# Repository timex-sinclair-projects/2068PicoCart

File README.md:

# 2068 PicoCart

A dock cartridge for the Timex Sinclair 2068, built around a Raspberry Pi RP2354B (RP2350 with 2 MB of flash in the package). It emulates the cartridge ROM and RAM in the dock bank. To load a cart, plug the cart into your computer with USB-C and copy a `.dck` or `.bin` file onto it as if it were a thumb drive.

| Top | Bottom |
|:---:|:---:|
|  |  |

## Features

- **Thumb-drive loading.** Over USB the cart appears as a 1.4 MB drive called `PICOCART`. Copy a cart onto it, then switch the 2068 off and on. The cart serves the file you copied most recently and remembers it across power cycles.
- **A cartridge icon on the Mac.** In the Finder the `PICOCART` drive shows a cartridge icon ([`firmware/romemu/icon`](firmware/romemu/icon)). The firmware adds the two hidden files that make it, `.VolumeIcon.icns` and `._.`, whenever they're missing.
- **AROS and LROS images.** Supports `.dck` files (the EightyOne/Warajevo dock format, including RAM chunks) and raw `.bin`/`.rom` images. A raw image loads at $8000 unless its name gives an address, for example `GAME@0000.BIN`.
- **Full-speed bus emulation.** One RP2350 core does nothing but serve the bus. It runs from SRAM with interrupts off and handles about 650,000 dock reads per second in the 2068.
- **On-screen cart menu.** Hold **MENU** while switching the 2068 on, and it shows a list of the carts on the drive. Pick one with the cursor keys (or Q/A) and ENTER, and the 2068 restarts into that cart, with no power cycle. Pressing MENU while the 2068 runs brings the menu up at the next power-up instead, even with no USB power in between. The first entry starts the 2068 in BASIC with the cart off the bus.
- **No USB needed in the 2068.** The cart runs on the 2068's own +5 V. USB is only for copying carts onto it, and the cart can be powered by USB alone for that.
- **Safe on the bus.** The 74LVC245 data buffer stays off until the cart sees the 2068's +5 V hold steady.
- **USB serial.** Status and debug output come over the same USB-C cable. `picotool load -f` can reflash the cart without pressing BOOTSEL.

## Hardware

- 4-layer board: signal, GND, +3V3, signal. KiCad 10 project in [`hardware/`](hardware).
- RP2354B, 74LVC245 buffer on the data bus, a 74LVC1G332 for buffer enable, a 3.3 V LDO, USB-C, and two buttons: MENU and BOOTSEL.
- Red LED = cart on the bus. White LED = dock activity. R15, the white LED's resistor, is 3.3 kΩ; rev 0.1 boards have 100 Ω.
- The board and the routing are generated by scripts in [`hardware/scripts`](hardware/scripts). The pinout and BOM are in [SCHEMATIC.md](SCHEMATIC.md); the design notes are in [PLAN.md](PLAN.md).
- JLCPCB Gerbers, BOM and placement file for **rev 0.2** are in [`hardware/fab/jlcpcb`](hardware/fab/jlcpcb). Rev 0.2 differs from rev 0.1 in the MENU/BOOT labels, R15 = 3.3 kΩ, no OLED header, and "rev 0.2" on the underside. Read [hardware/fab/NOTES.md](hardware/fab/NOTES.md) before ordering. It covers the finger bevel, the parts that aren't assembled, and the L1 orientation.

### GPIO map

| GPIO | Signal |
|---|---|
| 0–15 | A0–A15 |
| 16–23 | MD0–MD7 (MCU side of the 74LVC245) |
| 24–31 | ROSCS, MREQ, RD, WR, IORQ, M1, RFSH, EXROM |
| 32 | BUS_OFF (high = buffer off) |
| 33 | BE (via the R10 link, not fitted) |
| 37 | A7R |
| 40 / 41 | DOCK +5 V and VBUS sense (ADC, 10k/15k dividers) |
| 43 / 44 | White / red LED |
| 45 | MENU button |
| 46 / 47 | UART TX / RX (test pads) |

## Firmware

Two programs are in [`firmware/`](firmware). Both use the board header in [`firmware/boards`](firmware/boards):

- [`bringup`](firmware/bringup) checks a new board. It holds the bus buffer off, then reports the +5 V rails, activity on the bus lines, and the MD float test over USB serial.
- [`romemu`](firmware/romemu) is the cartridge firmware. The cart menu is Z80 code in [`romemu/menu`](firmware/romemu/menu). The build reassembles it with [sjasmplus](https://github.com/z00m128/sjasmplus) when that's installed, and otherwise uses the committed `menu.bin`.

### Bus behaviour

[BUS.md](BUS.md) sets out exactly when the cart drives the 2068's buses, with references to the schematic and firmware. Read it if you're combining the cart with other hardware on the bus, such as a TS-Pico on the rear expansion port.

### How the menu works

The menu is a machine-code AROS cart that the firmware serves at $8000, with a directory table at $9000 that lists the carts on the drive. When you choose one, the menu copies a short routine into HOME RAM and runs it from there. The routine writes the entry number to $BFFF in the dock, the cart's mailbox. It then waits about a second while the firmware swaps in the chosen cart, pages HOME back in and jumps to $0000. The 2068 starts up again and reads the new cart's header. [`firmware/tests/menu_dck.py`](firmware/tests/menu_dck.py) builds the menu with a test directory as a `.dck`, for trying it in an emulator such as ZEsarUX.

### Build

You need the Pico SDK 2.2.0 or later, the Arm GNU toolchain, CMake, Ninja and picotool.

```bash
export PICO_SDK_PATH=~/pico-sdk PICO_TOOLCHAIN_PATH=~/arm-gnu-toolchain
cmake -S firmware/romemu -B firmware/romemu/build -G Ninja
ninja -C firmware/romemu/build
picotool load -f -x firmware/romemu/build/romemu.uf2
```

The first time, hold BOOTSEL while plugging in USB; after that, `picotool load -f` reboots the cart itself.

The white LED (D4) runs at 3% brightness by default, to suit rev 0.1 boards, where R15 is 100 Ω. On boards built from the current design (R15 = 3.3 kΩ), build with `-DLED2_PERCENT=100`:

```bash
cmake -S firmware/romemu -B firmware/romemu/build -DLED2_PERCENT=100
```

Optionally, you can compile a fallback image into the firmware. The cart serves it when the drive has no cart on it:

```bash
cmake -S firmware/romemu -B firmware/romemu/build -DROM_IMAGE="path/to/cart.dck"
```

### Flash layout

| Offset | Use |
|---|---|
| 0x000000 | Firmware (up to 512 KB) |
| 0x080000 | `PICOCART` drive: FAT12, 1.4 MB |
| 0x1FE000 | Settings log, two 4 KB sectors: the current cart, and whether the menu comes up at the next power-up |

On first boot the firmware formats the drive and puts a `README.TXT` on it. If the drive gets corrupted, reformat it from your computer as FAT.

## Using it

The full user's manual is in [`docs/manual`](docs/manual): [read it on screen](docs/manual/2068%20PicoCart%20Manual.html), or print the [half-letter PDF](docs/manual/2068%20PicoCart%20Manual%20(half-letter).pdf) or the [duplex booklet](docs/manual/2068%20PicoCart%20Manual%20(booklet,%20print%20duplex).pdf). For a booklet with a card cover, print the [card-cover booklet](docs/manual/2068%20PicoCart%20Manual%20(booklet%20with%20card%20cover,%20print%20duplex).pdf): its first sheet is the cover, with blank inside covers, so you can print that sheet on card.

1. Plug the cart into your computer. The `PICOCART` drive appears.
2. Copy a `.dck`, `.bin` or `.rom` file onto it, then eject the drive.
3. Switch the 2068 off and on. The 2068 reads the dock only at power-up.

If the 2068 is running when you copy, the cart keeps serving the old cart until the 2068 is switched off. Both LEDs blink together while a new cart is waiting.

To switch between carts already on the drive, hold MENU while switching the 2068 on and pick one from the list. The cart you pick stays the current cart until you pick or copy another.

### Without USB

The cart doesn't need USB in the 2068. It runs on the 2068's +5 V and remembers everything in flash: the carts on the drive, the current cart, and a MENU press made while the 2068 was on. So you can fill the drive once and leave the cable at your computer:

1. Plug the cart into your computer on its own, with no 2068. USB powers it, and the `PICOCART` drive appears.
2. Copy carts onto it, eject the drive and unplug the cable.
3. Put the cart in the 2068 and switch it on. Choose carts with the menu.

From the 2068's power alone, the cart's firmware is running 0.1 ms after power reaches it, and the cart serves the bus about 1.8 s before the 2068 first reads the dock. You can plug USB in while the 2068 is on, for example to watch the serial status; the cart keeps running.

## Status

Rev 0.1 boards have been built and brought up. These carts run from the cart's ROM: AROS BASIC carts (Hello world, and Profile 2068's 16K at $8000–$BFFF), 32K machine-code carts (73000 Flight Simulator), and LROS carts that replace the HOME ROM (Space Raiders, 16K at $0000–$3FFF). RAM in the dock bank works: [`firmware/tests/ramtest.py`](firmware/tests/ramtest.py) builds a test cart that writes and checks two patterns across 8 KB of cart RAM at $C000. It passes, and the cart counted exactly 16,384 dock writes. Loading from the USB drive works. The cart runs on the 2068's power alone, with no USB. The on-screen cart menu works on the 2068: choosing a cart restarts the 2068 into it, and the "no cartridge" entry starts BASIC with the cart off the bus. Pressing MENU while a cart runs brings up the menu at the next power-up, with or without USB power in between, and a second press cancels it. Every feature has now been tested on hardware.

Rev 0.2 is designed but not yet built. Its fab files are in [`hardware/fab/jlcpcb`](hardware/fab/jlcpcb). The changes are small and come from using rev 0.1:
- MENU and BOOT labels on the silkscreen by the buttons.
- R15, the white LED's resistor, is 3.3 kΩ instead of 100 Ω. At 100 Ω the white LED was far brighter than the red one; rev 0.1 firmware dims it to 3% with PWM instead. Build the firmware for rev 0.2 with `-DLED2_PERCENT=100`.
- No OLED header. The dock covers that part of the board, so a display there could not be seen. GPIO34 and GPIO35 are now spare.
- "2068 PicoCart rev 0.2" on the underside, so the two revisions can be told apart.

The circuit and routing are otherwise the same as rev 0.1, so rev 0.2 should behave the same. Still to check when the boards arrive: the white LED's brightness at 3.3 kΩ.

## License

The hardware is licensed under [CERN-OHL-P-2.0](hardware/LICENSE) and the firmware under [MIT](firmware/LICENSE). See [LICENSE.md](LICENSE.md) for details.

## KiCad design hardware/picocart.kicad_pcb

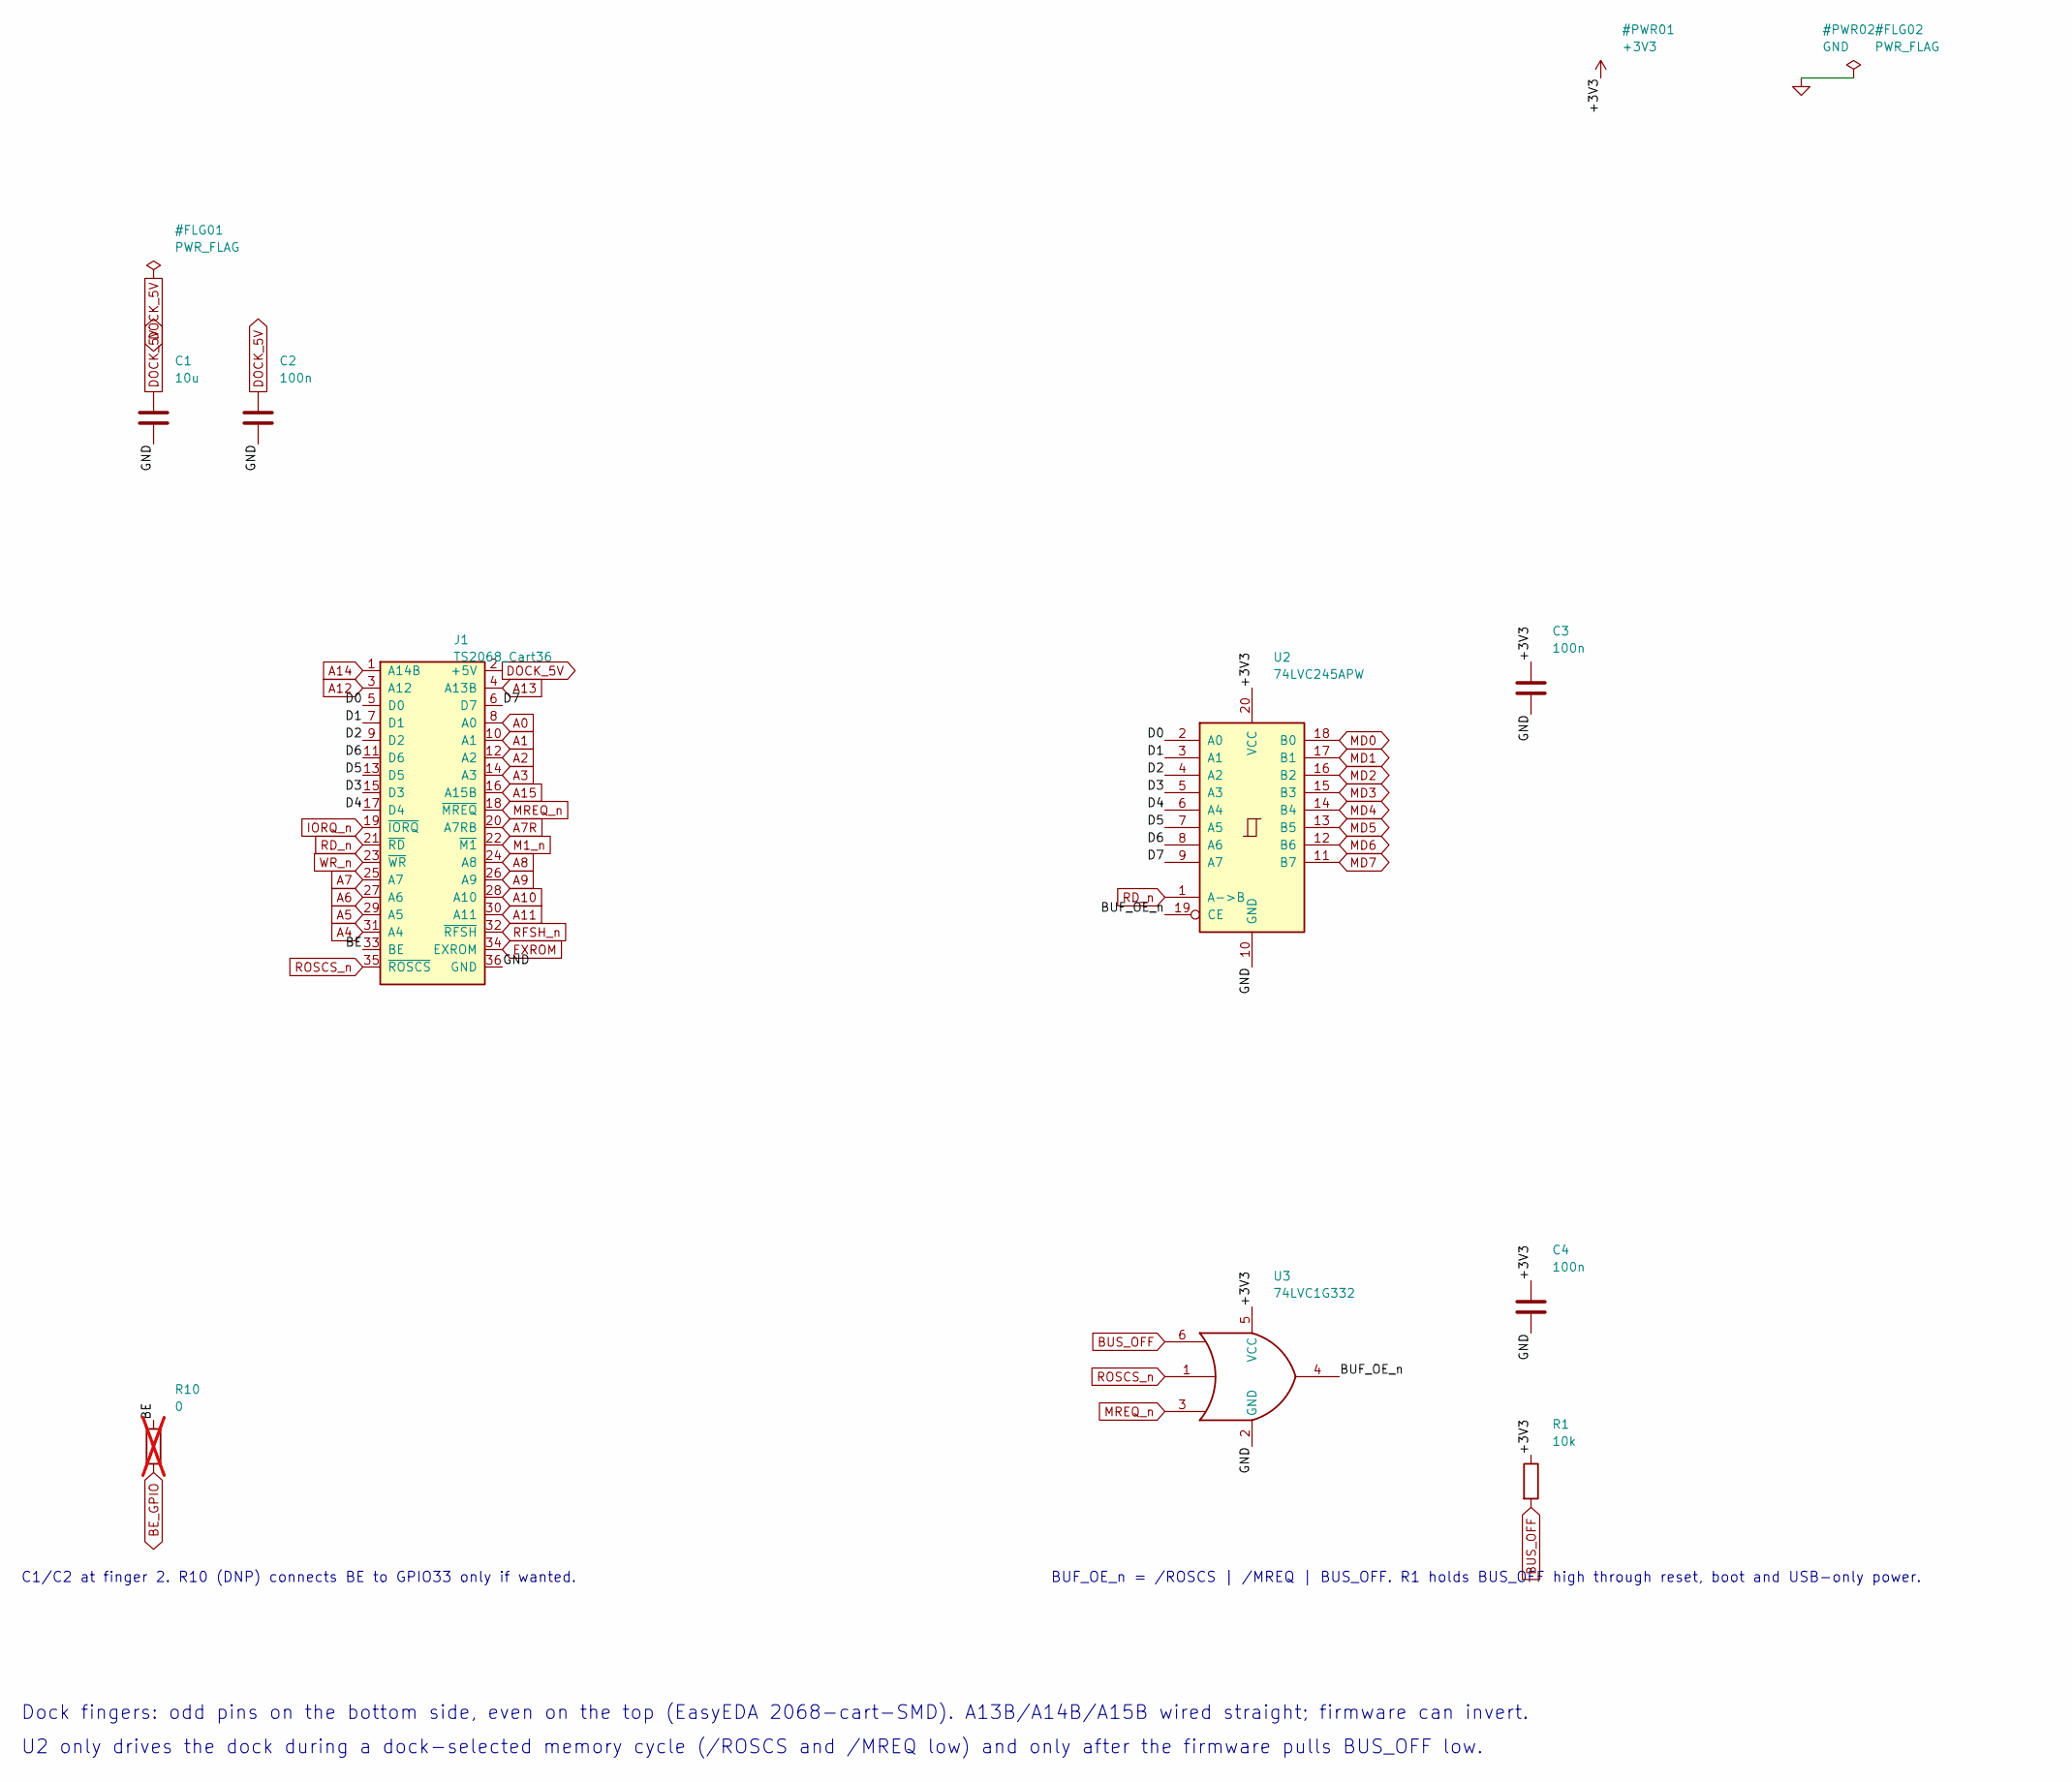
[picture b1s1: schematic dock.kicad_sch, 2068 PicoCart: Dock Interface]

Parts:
C1: 10u; C_0805_2012Metric; MPN CL21A106KAYNNNE; LCSC C15850
C2, C3, C4: 100n; C_0603_1608Metric; MPN CC0603KRX7R9BB104; LCSC C14663
J1: TS2068_Cart36
R1: 10k; R_0603_1608Metric; MPN 0603WAF1002T5E; LCSC C25804
R10: 0; R_0603_1608Metric; MPN 0603WAF0000T5E; LCSC C21189; not fitted
U2: 74LVC245APW; TSSOP-20_4.4x6.5mm_P0.65mm; MPN 74LVC245APW,118; LCSC C6082
U3: 74LVC1G332; SOT-363_SC-70-6; MPN 74LVC1G332GW,125; LCSC C548342

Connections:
+3V3: C3.1, C4.1, R1.1, U2.20 (VCC), U3.5 (VCC); also elsewhere on the board
/Dock Interface/BE: J1.33 (BE), R10.1
/Dock Interface/BUF_OE_n: U2.19 (CE), U3.4
/Dock Interface/D0: J1.5 (D0), U2.2 (A0)
/Dock Interface/D1: J1.7 (D1), U2.3 (A1)
/Dock Interface/D2: J1.9 (D2), U2.4 (A2)
/Dock Interface/D3: J1.15 (D3), U2.5 (A3)
/Dock Interface/D4: J1.17 (D4), U2.6 (A4)
/Dock Interface/D5: J1.13 (D5), U2.7 (A5)
/Dock Interface/D6: J1.11 (D6), U2.8 (A6)
/Dock Interface/D7: J1.6 (D7), U2.9 (A7)
A0: J1.8 (A0); also elsewhere on the board
A1: J1.10 (A1); also elsewhere on the board
A2: J1.12 (A2); also elsewhere on the board
A3: J1.14 (A3); also elsewhere on the board
A4: J1.31 (A4); also elsewhere on the board
A5: J1.29 (A5); also elsewhere on the board
A6: J1.27 (A6); also elsewhere on the board
A7: J1.25 (A7); also elsewhere on the board
A7R: J1.20 (A7RB); also elsewhere on the board
A8: J1.24 (A8); also elsewhere on the board
A9: J1.26 (A9); also elsewhere on the board
A10: J1.28 (A10); also elsewhere on the board
A11: J1.30 (A11); also elsewhere on the board
A12: J1.3 (A12); also elsewhere on the board
A13: J1.4 (A13B); also elsewhere on the board
A14: J1.1 (A14B); also elsewhere on the board
A15: J1.16 (A15B); also elsewhere on the board
BE_GPIO: R10.2; also elsewhere on the board
BUS_OFF: R1.2, U3.6; also elsewhere on the board
DOCK_5V: C1.1, C2.1, J1.2 (+5V); also elsewhere on the board
EXROM: J1.34 (EXROM); also elsewhere on the board
GND: C1.2, C2.2, C3.2, C4.2, J1.36 (GND), U2.10 (GND), U3.2 (GND); also elsewhere on the board
IORQ_n: J1.19 (~IORQ); also elsewhere on the board
M1_n: J1.22 (~M1); also elsewhere on the board
MD0: U2.18 (B0); also elsewhere on the board
MD1: U2.17 (B1); also elsewhere on the board
MD2: U2.16 (B2); also elsewhere on the board
MD3: U2.15 (B3); also elsewhere on the board
MD4: U2.14 (B4); also elsewhere on the board
MD5: U2.13 (B5); also elsewhere on the board
MD6: U2.12 (B6); also elsewhere on the board
MD7: U2.11 (B7); also elsewhere on the board
MREQ_n: J1.18 (~MREQ), U3.3; also elsewhere on the board
RD_n: J1.21 (~RD), U2.1 (A->B); also elsewhere on the board
RFSH_n: J1.32 (~RFSH); also elsewhere on the board
ROSCS_n: J1.35 (~ROSCS), U3.1; also elsewhere on the board
WR_n: J1.23 (~WR); also elsewhere on the board

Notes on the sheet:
Dock fingers: odd pins on the bottom side, even on the top (EasyEDA 2068-cart-SMD). A13B/A14B/A15B wired straight; firmware can invert.
U2 only drives the dock during a dock-selected memory cycle (/ROSCS and /MREQ low) and only after the firmware pulls BUS_OFF low.
C1/C2 at finger 2. R10 (DNP) connects BE to GPIO33 only if wanted.
BUF_OE_n = /ROSCS | /MREQ | BUS_OFF. R1 holds BUS_OFF high through reset, boot and USB-only power.

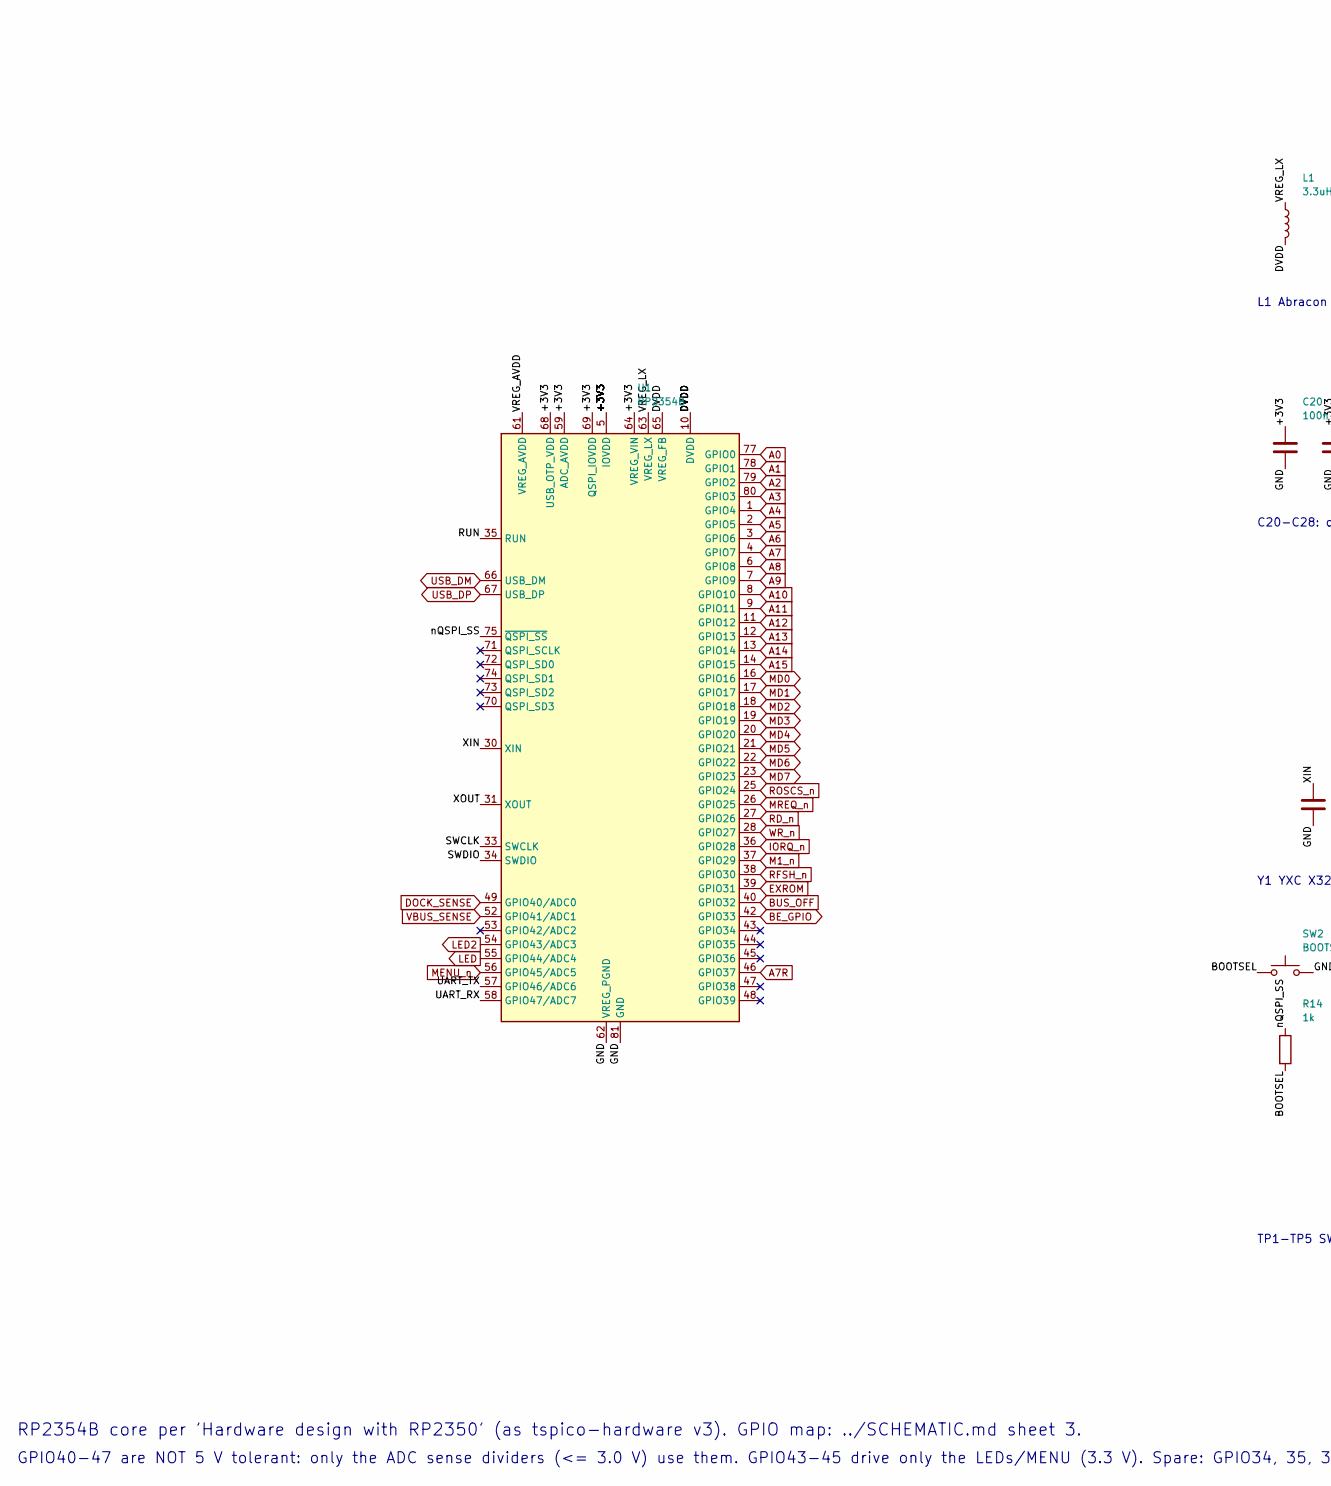
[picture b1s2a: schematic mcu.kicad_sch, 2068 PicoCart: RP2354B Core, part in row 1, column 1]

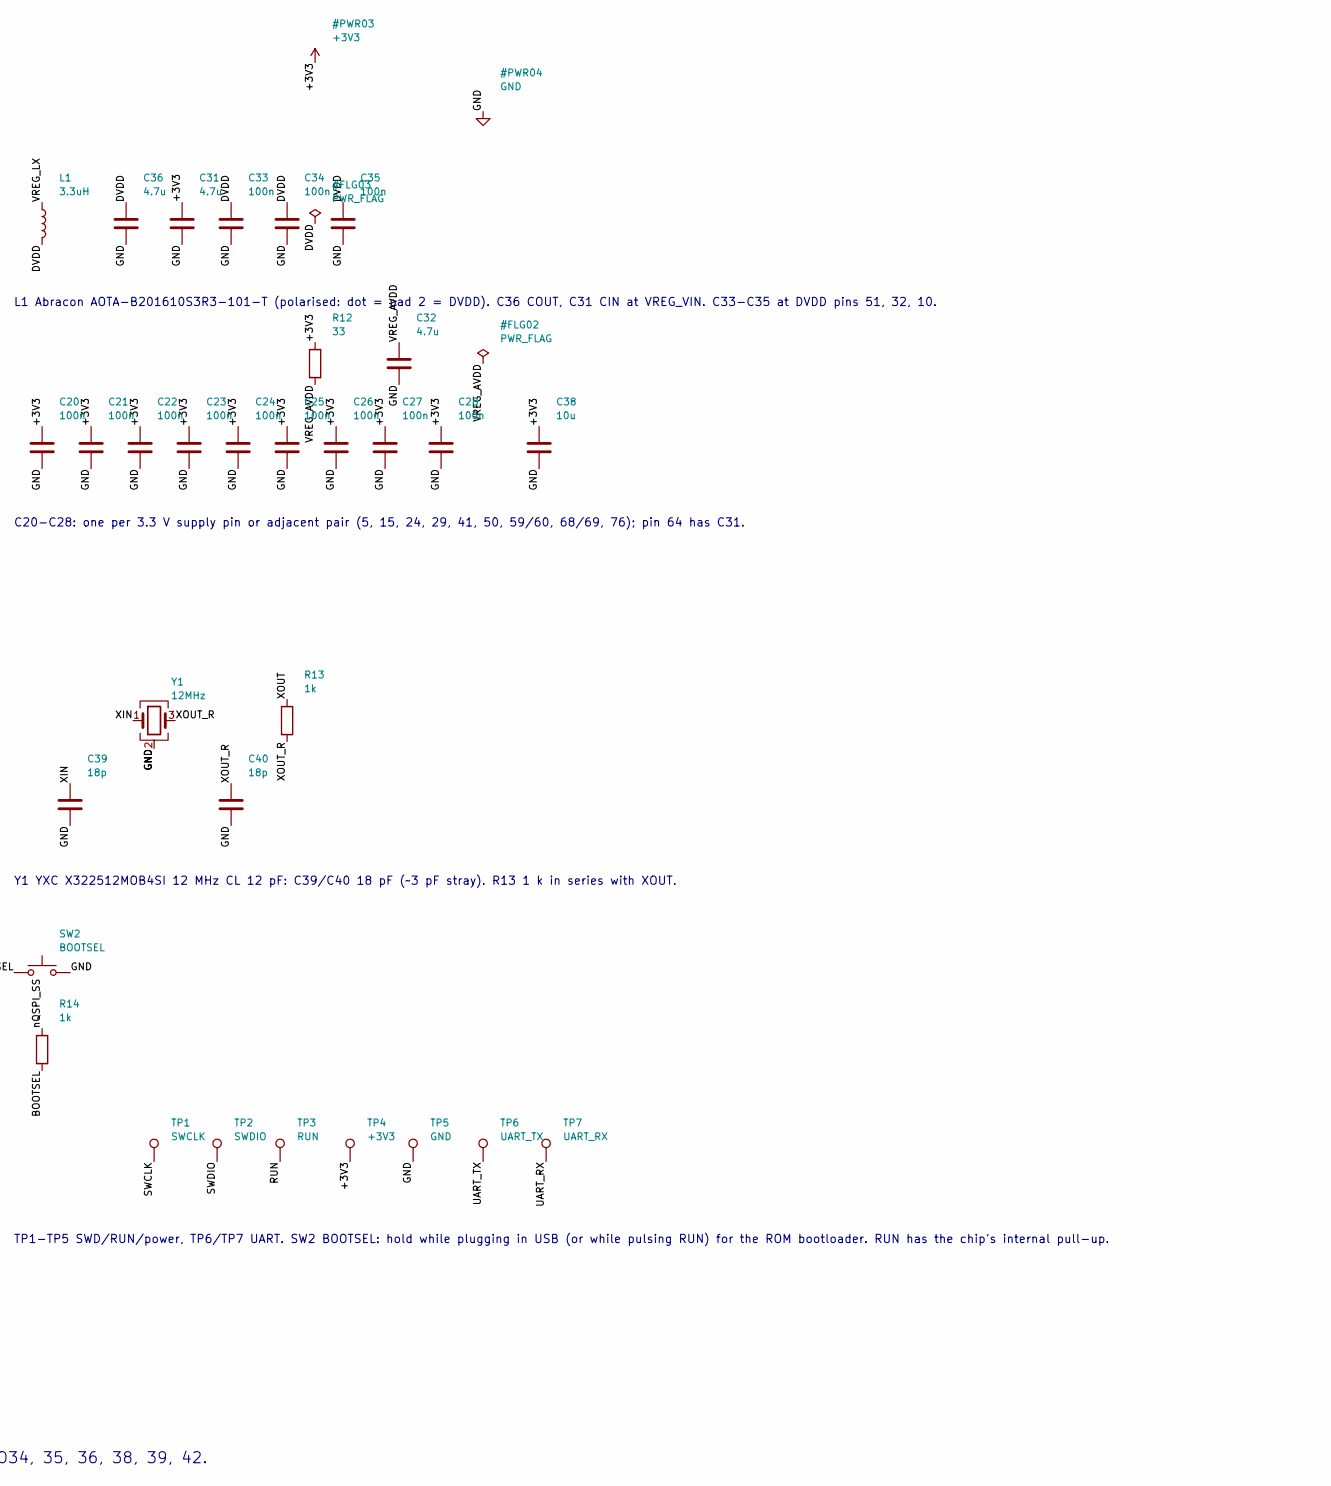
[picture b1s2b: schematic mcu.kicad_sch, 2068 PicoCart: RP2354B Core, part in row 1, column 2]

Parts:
C20, C21, C22, C23, C24, C25, C26, C27, C28, C33, C34, C35: 100n; C_0603_1608Metric; MPN CC0603KRX7R9BB104; LCSC C14663
C31, C32, C36: 4.7u; C_0402_1005Metric; MPN CL05A475MP5NRNC; LCSC C23733
C38: 10u; C_0603_1608Metric; MPN CL10A106KP8NNNC; LCSC C19702
C39, C40: 18p; C_0603_1608Metric; MPN CL10C180JB8NNNC; LCSC C1647
L1: 3.3uH; L_Abracon_AOTA-B201610; MPN AOTA-B201610S3R3-101-T; LCSC C42411119
R12: 33; R_0603_1608Metric; MPN 0603WAF330JT5E; LCSC C23140
R13, R14: 1k; R_0603_1608Metric; MPN 0603WAF1001T5E; LCSC C21190
SW2: BOOTSEL; SW_Push_1P1T_XKB_TS-1187A; MPN TS-1187A-C-J-B; LCSC C318885
TP1: SWCLK; TestPoint_Pad_1.0x1.0mm
TP2: SWDIO; TestPoint_Pad_1.0x1.0mm
TP3: RUN; TestPoint_Pad_1.0x1.0mm
TP4: +3V3; TestPoint_Pad_1.0x1.0mm
TP5: GND; TestPoint_Pad_1.0x1.0mm
TP6: UART_TX; TestPoint_Pad_1.0x1.0mm
TP7: UART_RX; TestPoint_Pad_1.0x1.0mm
U1: RP2354B; QFN-80-1EP_10x10mm_P0.4mm_EP3.4x3.4mm; MPN RP2354B; LCSC C39843328
Y1: 12MHz; Crystal_SMD_3225-4Pin_3.2x2.5mm; MPN X322512MOB4SI; LCSC C70565

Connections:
+3V3: C20.1, C21.1, C22.1, C23.1, C24.1, C25.1, C26.1, C27.1, C28.1, C31.1, C38.1, R12.1, TP4.1, U1.5 (IOVDD), U1.15 (IOVDD), U1.24 (IOVDD), U1.29 (IOVDD), U1.41 (IOVDD), U1.50 (IOVDD), U1.59 (ADC_AVDD), U1.60 (IOVDD), U1.64 (VREG_VIN), U1.68 (USB_OTP_VDD), U1.69 (QSPI_IOVDD), U1.76 (IOVDD); also elsewhere on the board
/RP2354B Core/BOOTSEL: R14.2, SW2.1
/RP2354B Core/DVDD: C33.1, C34.1, C35.1, C36.1, L1.2, U1.10 (DVDD), U1.32 (DVDD), U1.51 (DVDD), U1.65 (VREG_FB)
/RP2354B Core/RUN: TP3.1, U1.35 (RUN)
/RP2354B Core/SWCLK: TP1.1, U1.33 (SWCLK)
/RP2354B Core/SWDIO: TP2.1, U1.34 (SWDIO)
/RP2354B Core/UART_RX: TP7.1, U1.58 (GPIO47/ADC7)
/RP2354B Core/UART_TX: TP6.1, U1.57 (GPIO46/ADC6)
/RP2354B Core/VREG_AVDD: C32.1, R12.2, U1.61 (VREG_AVDD)
/RP2354B Core/VREG_LX: L1.1, U1.63 (VREG_LX)
/RP2354B Core/XIN: C39.1, U1.30 (XIN), Y1.1
/RP2354B Core/XOUT: R13.1, U1.31 (XOUT)
/RP2354B Core/XOUT_R: C40.1, R13.2, Y1.3
/RP2354B Core/nQSPI_SS: R14.1, U1.75 (~QSPI_SS)
A0: U1.77 (GPIO0); also elsewhere on the board
A1: U1.78 (GPIO1); also elsewhere on the board
A2: U1.79 (GPIO2); also elsewhere on the board
A3: U1.80 (GPIO3); also elsewhere on the board
A4: U1.1 (GPIO4); also elsewhere on the board
A5: U1.2 (GPIO5); also elsewhere on the board
A6: U1.3 (GPIO6); also elsewhere on the board
A7: U1.4 (GPIO7); also elsewhere on the board
A7R: U1.46 (GPIO37); also elsewhere on the board
A8: U1.6 (GPIO8); also elsewhere on the board
A9: U1.7 (GPIO9); also elsewhere on the board
A10: U1.8 (GPIO10); also elsewhere on the board
A11: U1.9 (GPIO11); also elsewhere on the board
A12: U1.11 (GPIO12); also elsewhere on the board
A13: U1.12 (GPIO13); also elsewhere on the board
A14: U1.13 (GPIO14); also elsewhere on the board
A15: U1.14 (GPIO15); also elsewhere on the board
BE_GPIO: U1.42 (GPIO33); also elsewhere on the board
BUS_OFF: U1.40 (GPIO32); also elsewhere on the board
DOCK_SENSE: U1.49 (GPIO40/ADC0); also elsewhere on the board
EXROM: U1.39 (GPIO31); also elsewhere on the board
GND: C20.2, C21.2, C22.2, C23.2, C24.2, C25.2, C26.2, C27.2, C28.2, C31.2, C32.2, C33.2, C34.2, C35.2, C36.2, C38.2, C39.2, C40.2, SW2.2, TP5.1, U1.62 (VREG_PGND), U1.81 (GND), Y1.2 (G), Y1.4 (G); also elsewhere on the board
IORQ_n: U1.36 (GPIO28); also elsewhere on the board
LED: U1.55 (GPIO44/ADC4); also elsewhere on the board
LED2: U1.54 (GPIO43/ADC3); also elsewhere on the board
M1_n: U1.37 (GPIO29); also elsewhere on the board
MD0: U1.16 (GPIO16); also elsewhere on the board
MD1: U1.17 (GPIO17); also elsewhere on the board
MD2: U1.18 (GPIO18); also elsewhere on the board
MD3: U1.19 (GPIO19); also elsewhere on the board
MD4: U1.20 (GPIO20); also elsewhere on the board
MD5: U1.21 (GPIO21); also elsewhere on the board
MD6: U1.22 (GPIO22); also elsewhere on the board
MD7: U1.23 (GPIO23); also elsewhere on the board
MENU_n: U1.56 (GPIO45/ADC5); also elsewhere on the board
MREQ_n: U1.26 (GPIO25); also elsewhere on the board
RD_n: U1.27 (GPIO26); also elsewhere on the board
RFSH_n: U1.38 (GPIO30); also elsewhere on the board
ROSCS_n: U1.25 (GPIO24); also elsewhere on the board
USB_DM: U1.66 (USB_DM); also elsewhere on the board
USB_DP: U1.67 (USB_DP); also elsewhere on the board
VBUS_SENSE: U1.52 (GPIO41/ADC1); also elsewhere on the board
WR_n: U1.28 (GPIO27); also elsewhere on the board

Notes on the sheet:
RP2354B core per 'Hardware design with RP2350' (as tspico-hardware v3). GPIO map: ../SCHEMATIC.md sheet 3.
GPIO40-47 are NOT 5 V tolerant: only the ADC sense dividers (<= 3.0 V) use them. GPIO43-45 drive only the LEDs/MENU (3.3 V). Spare: GPIO34, 35, 36, 38, 39, 42.
L1 Abracon AOTA-B201610S3R3-101-T (polarised: dot = pad 2 = DVDD). C36 COUT, C31 CIN at VREG_VIN. C33-C35 at DVDD pins 51, 32, 10.
C20-C28: one per 3.3 V supply pin or adjacent pair (5, 15, 24, 29, 41, 50, 59/60, 68/69, 76); pin 64 has C31.
Y1 YXC X322512MOB4SI 12 MHz CL 12 pF: C39/C40 18 pF (~3 pF stray). R13 1 k in series with XOUT.
TP1-TP5 SWD/RUN/power, TP6/TP7 UART. SW2 BOOTSEL: hold while plugging in USB (or while pulsing RUN) for the ROM bootloader. RUN has the chip's internal pull-up.

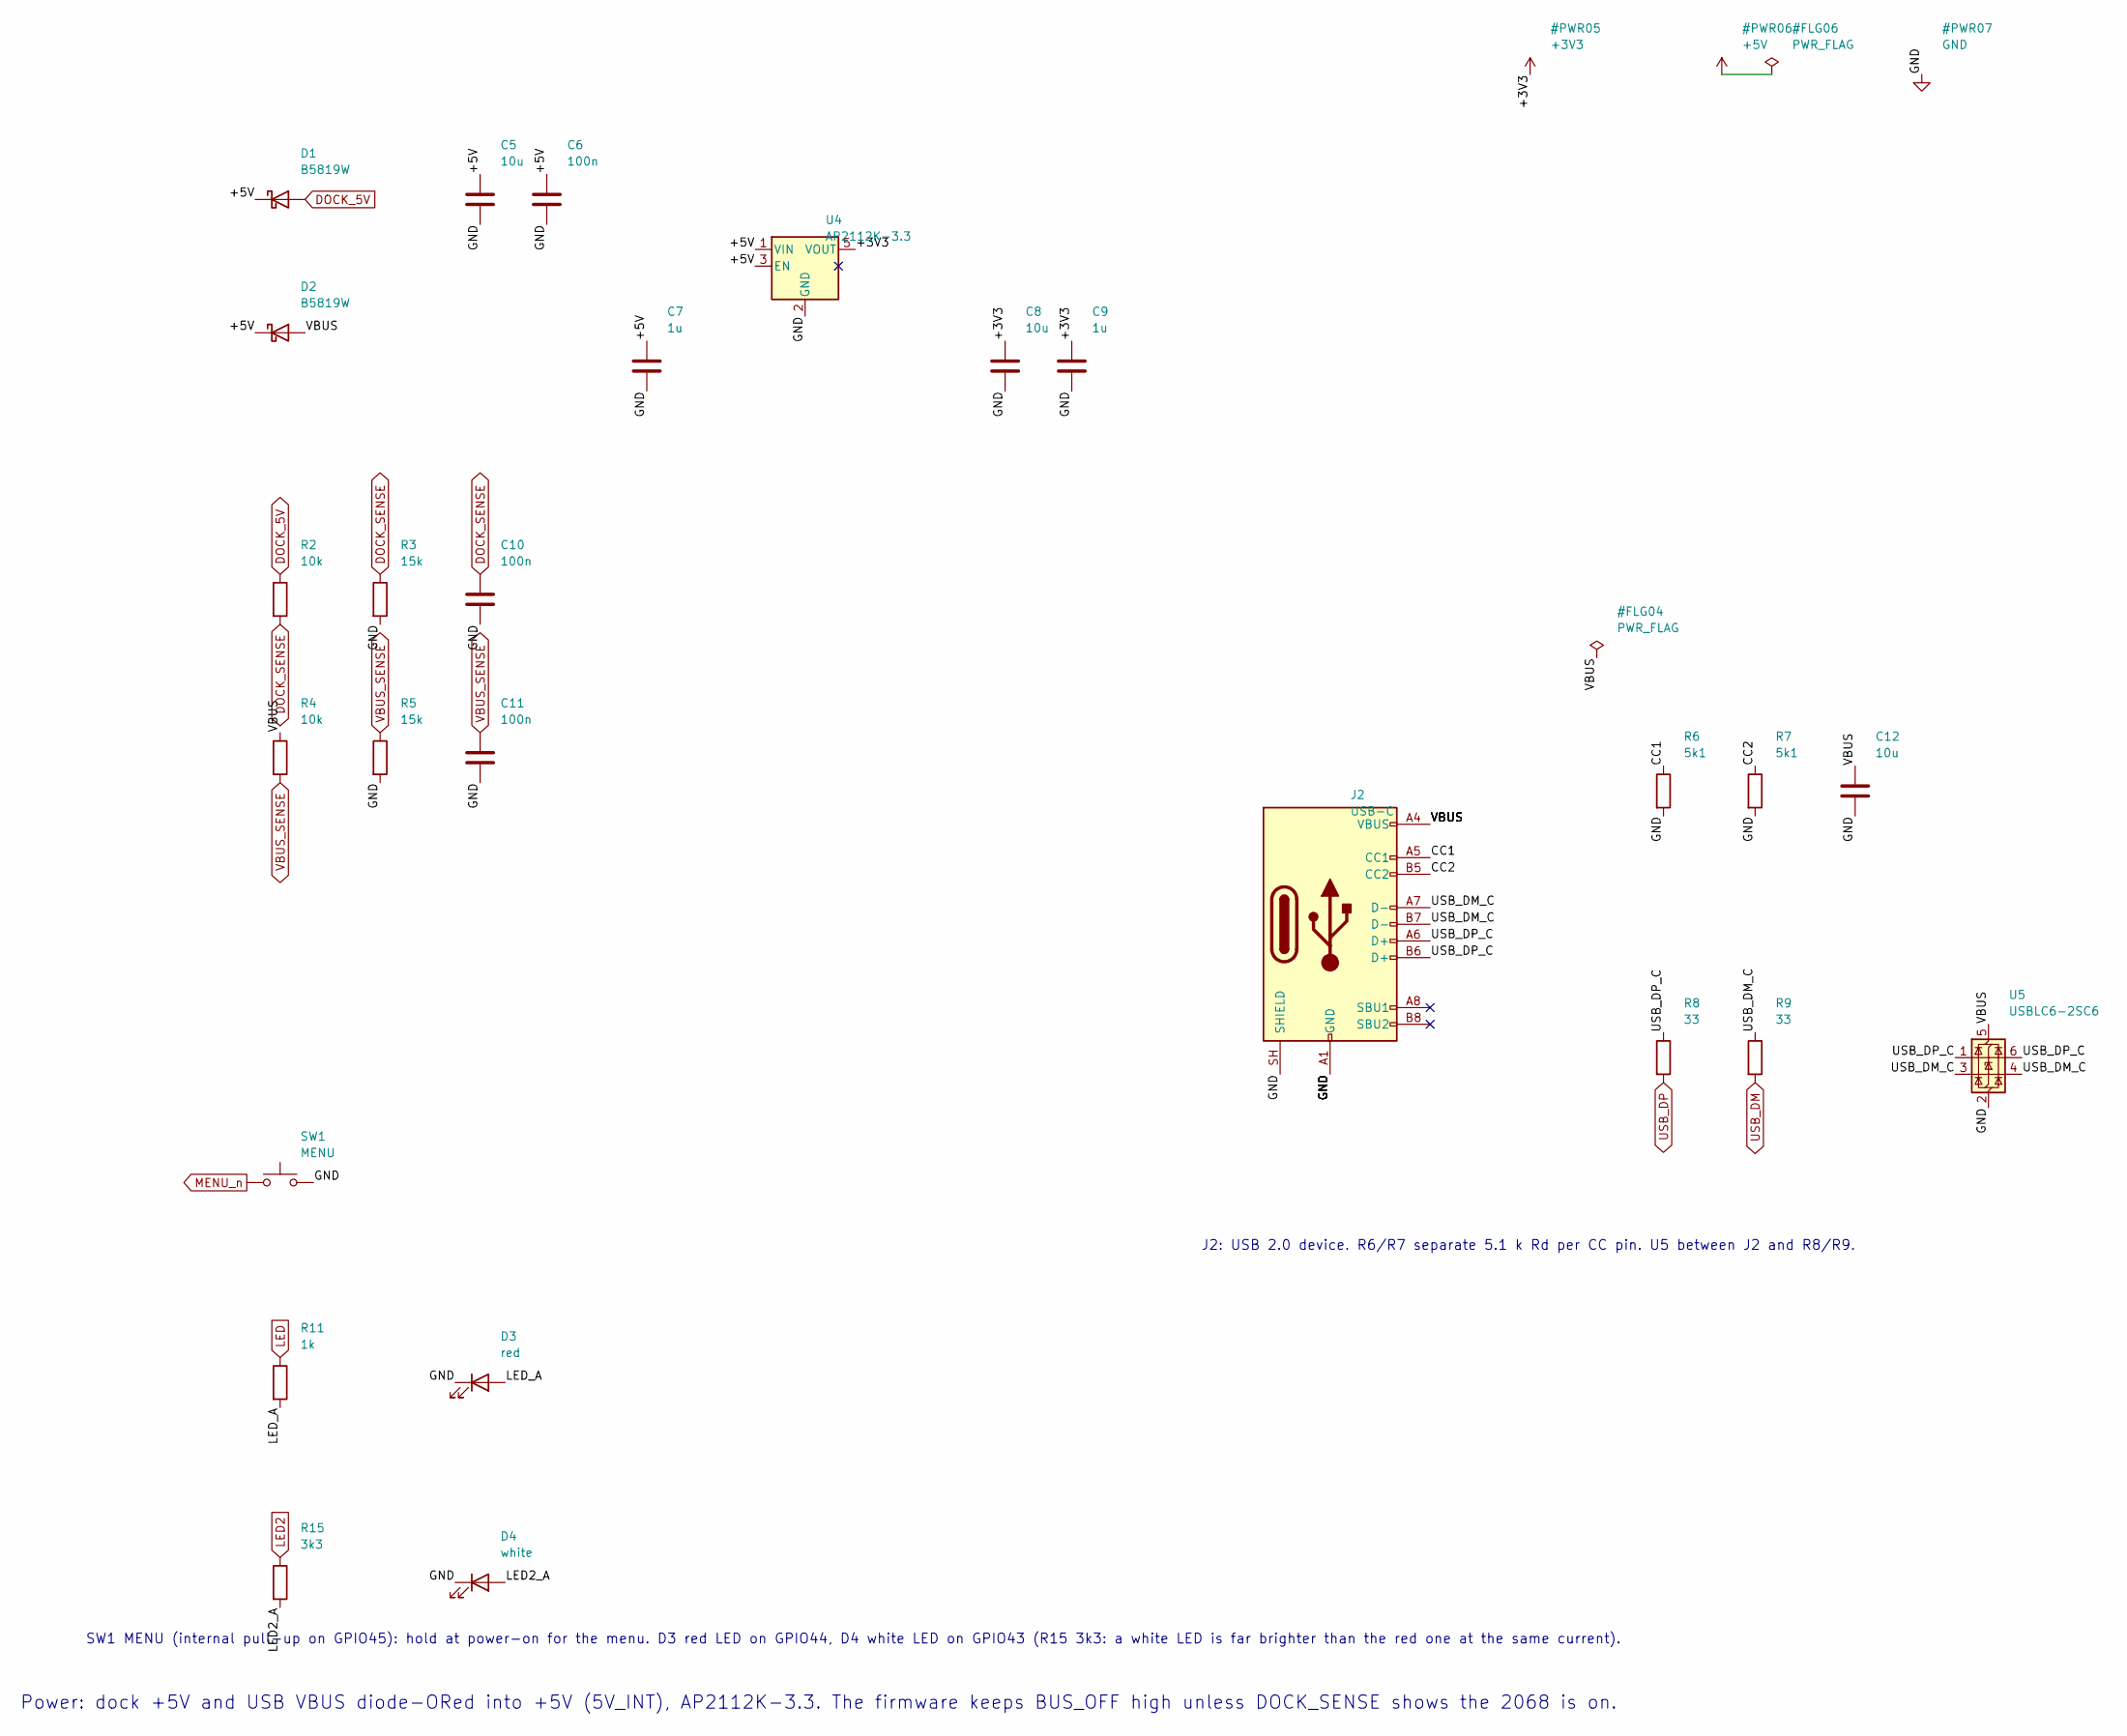
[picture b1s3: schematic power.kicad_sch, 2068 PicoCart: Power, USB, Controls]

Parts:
C5, C12: 10u; C_0805_2012Metric; MPN CL21A106KAYNNNE; LCSC C15850
C6, C10, C11: 100n; C_0603_1608Metric; MPN CC0603KRX7R9BB104; LCSC C14663
C7, C9: 1u; C_0603_1608Metric; MPN CL10A105KB8NNNC; LCSC C15849
C8: 10u; C_0603_1608Metric; MPN CL10A106KP8NNNC; LCSC C19702
D1, D2: B5819W; D_SOD-123; MPN B5819W SL; LCSC C8598
D3: red; LED_0603_1608Metric; MPN KT-0603R; LCSC C2286
D4: white; LED_0603_1608Metric; MPN KT-0603W; LCSC C2290
J2: USB-C; USB_C_Receptacle_HRO_TYPE-C-31-M-12; MPN HX TYPE-C 16PIN; LCSC C5178539
R2, R4: 10k; R_0603_1608Metric; MPN 0603WAF1002T5E; LCSC C25804
R3, R5: 15k; R_0603_1608Metric; MPN 0603WAF1502T5E; LCSC C22809
R6, R7: 5k1; R_0603_1608Metric; MPN 0603WAF5101T5E; LCSC C23186
R8, R9: 33; R_0603_1608Metric; MPN 0603WAF330JT5E; LCSC C23140
R11: 1k; R_0603_1608Metric; MPN 0603WAF1001T5E; LCSC C21190
R15: 3k3; R_0603_1608Metric; MPN 0603WAF3301T5E; LCSC C22978
SW1: MENU; SW_Push_1P1T_XKB_TS-1187A; MPN TS-1187A-C-J-B; LCSC C318885
U4: AP2112K-3.3; SOT-23-5; MPN AP2112K-3.3TRG1; LCSC C51118
U5: USBLC6-2SC6; SOT-23-6; MPN USBLC6-2SC6; LCSC C7519

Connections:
+3V3: C8.1, C9.1, U4.5 (VOUT); also elsewhere on the board
+5V: C5.1, C6.1, C7.1, D1.1 (K), D2.1 (K), U4.1 (VIN), U4.3 (EN)
/Power, USB, Controls/CC1: J2.A5 (CC1), R6.1
/Power, USB, Controls/CC2: J2.B5 (CC2), R7.1
/Power, USB, Controls/LED2_A: D4.2 (A), R15.2
/Power, USB, Controls/LED_A: D3.2 (A), R11.2
/Power, USB, Controls/USB_DM_C: J2.A7 (D-), J2.B7 (D-), R9.1, U5.3 (I/O2), U5.4 (I/O2)
/Power, USB, Controls/USB_DP_C: J2.A6 (D+), J2.B6 (D+), R8.1, U5.1 (I/O1), U5.6 (I/O1)
/Power, USB, Controls/VBUS: C12.1, D2.2 (A), J2.A4 (VBUS), J2.A9 (VBUS), J2.B4 (VBUS), J2.B9 (VBUS), R4.1, U5.5 (VBUS)
DOCK_5V: D1.2 (A), R2.1; also elsewhere on the board
DOCK_SENSE: C10.1, R2.2, R3.1; also elsewhere on the board
GND: C5.2, C6.2, C7.2, C8.2, C9.2, C10.2, C11.2, C12.2, D3.1 (K), D4.1 (K), J2.A1 (GND), J2.A12 (GND), J2.B1 (GND), J2.B12 (GND), J2.SH (SHIELD), R3.2, R5.2, R6.2, R7.2, SW1.2, U4.2 (GND), U5.2 (GND); also elsewhere on the board
LED: R11.1; also elsewhere on the board
LED2: R15.1; also elsewhere on the board
MENU_n: SW1.1; also elsewhere on the board
USB_DM: R9.2; also elsewhere on the board
USB_DP: R8.2; also elsewhere on the board
VBUS_SENSE: C11.1, R4.2, R5.1; also elsewhere on the board

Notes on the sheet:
Power: dock +5V and USB VBUS diode-ORed into +5V (5V_INT), AP2112K-3.3. The firmware keeps BUS_OFF high unless DOCK_SENSE shows the 2068 is on.
J2: USB 2.0 device. R6/R7 separate 5.1 k Rd per CC pin. U5 between J2 and R8/R9.
SW1 MENU (internal pull-up on GPIO45): hold at power-on for the menu. D3 red LED on GPIO44, D4 white LED on GPIO43 (R15 3k3: a white LED is far brighter than the red one at the same current).
